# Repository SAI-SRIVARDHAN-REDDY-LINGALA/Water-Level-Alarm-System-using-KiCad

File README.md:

# Water Level Alarm System using KiCad

## Overview

This project implements a simple and practical **Water Level Alarm System** designed using **KiCad PCB Design Suite**.

The system detects the presence of water using conductive sensing probes and activates an alarm or buzzer when water reaches a predefined level.

The project focuses on:

- Basic electronic sensing principles
- PCB schematic design
- PCB layout design
- Practical embedded hardware thinking
- Signal detection circuits
- Real-world safety and monitoring applications

The complete design was developed using:

- KiCad Schematic Editor
- KiCad PCB Layout Designer

---

# Features

- Water level detection
- Conductive probe sensing
- Alarm/buzzer indication
- Compact PCB design
- Practical low-cost implementation
- Real-world utility application
- PCB layout using KiCad
- Schematic capture
- Hardware-oriented design flow
- Beginner-friendly embedded electronics project

---

# Technologies Used

- KiCad EDA
- PCB Design
- Schematic Capture
- Electronic Circuit Design
- Sensor Interface Concepts
- Embedded Hardware Design

---

# Problem Statement

Water overflow in:

- tanks
- storage systems
- industrial containers
- home water systems

can cause:

- water wastage
- equipment damage
- electrical hazards

This project provides a simple electronic monitoring solution to alert users when water reaches a specific level.

---

# Working Principle

Water conducts electricity due to dissolved ions.

The system uses conductive probes placed at different water levels.

When water touches the sensing probes:

```text
Electrical path completes
        ↓
Detection circuit activates
        ↓
Alarm/Buzzer turns ON
```

---

# System Architecture

```text
Water Probes
      ↓
Detection Circuit
      ↓
Signal Activation
      ↓
Buzzer / Alarm
```

---

# Hardware Design Flow

The project follows a standard PCB development workflow:

```text
Circuit Design
      ↓
Schematic Capture
      ↓
Component Placement
      ↓
PCB Routing
      ↓
Design Rule Check (DRC)
      ↓
Final PCB Layout
```

---

# Schematic Design

The schematic includes:

- Water sensing probes
- Detection circuitry
- Output alarm device
- Power connections
- Signal routing

The design captures all electrical connectivity before PCB implementation.

---

# PCB Design

The PCB layout was developed in KiCad with focus on:

- Proper component placement
- Clean routing
- Electrical connectivity
- Compact board organization
- Manufacturable PCB structure

---

# PCB Design Concepts Covered

- PCB routing
- Component footprints
- Net connectivity
- Copper traces
- Signal paths
- Board layout planning
- Electrical rule validation
- Design Rule Check (DRC)

---

# Embedded Electronics Concepts Demonstrated

- Sensor-based detection
- Analog signal triggering
- Conductive sensing
- Alarm systems
- Hardware interfacing
- Practical electronic circuit behavior

---

# Skills Demonstrated

- KiCad PCB Design
- Schematic Capture
- PCB Layout Design
- Electronic Circuit Design
- Hardware System Thinking
- Sensor Interface Design
- Embedded Hardware Fundamentals
- Practical Electronics Prototyping

---

# Real-World Applications

This type of system is used in:

- Water tanks
- Industrial liquid monitoring
- Home automation systems
- Safety monitoring devices
- Overflow prevention systems
- Smart water management systems

---

# Engineering Importance

Although simple, this project introduces important hardware engineering workflows including:

- Schematic-to-PCB flow
- Real sensor interfacing
- Electrical connectivity planning
- Practical embedded system design
- Hardware debugging concepts

These are foundational skills for:

- Embedded systems engineering
- PCB design engineering
- Electronics product development
- IoT hardware systems

---

# Industry Relevance

The concepts demonstrated here are foundational to:

- Embedded electronics
- IoT sensing systems
- Industrial monitoring systems
- Consumer electronics hardware
- PCB-based product design

---

# Key Takeaways

- Water can be used as a conductive sensing medium
- PCB design begins with proper schematic capture
- KiCad provides a complete open-source PCB workflow
- Simple sensor systems require both electrical and physical design thinking
- Hardware design involves both circuit functionality and manufacturable layout planning

---

# Final Core Insight

```text
Sensor Detection
+
Signal Processing
+
PCB Implementation
=
Practical Embedded Hardware System
```

---

# Author

**Sai Srivardhan Lingala**  
Electronics Engineering Student | FPGA & Embedded Hardware Enthusiast

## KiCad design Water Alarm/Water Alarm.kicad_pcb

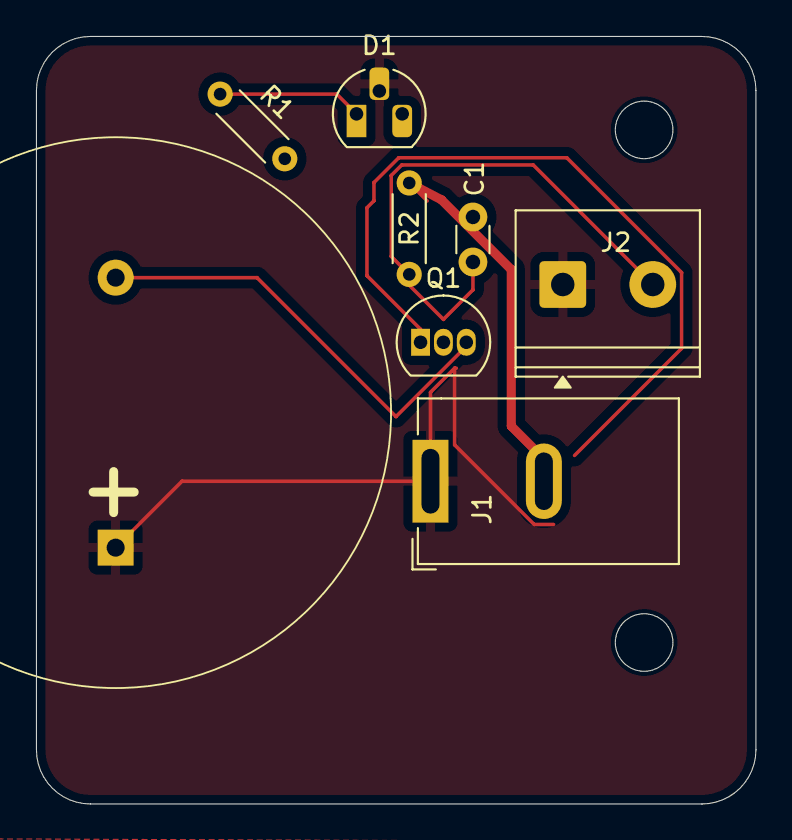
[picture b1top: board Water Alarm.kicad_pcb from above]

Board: 2 copper layers, 40.0 x 42.6 mm, 8 parts (0 on the bottom side), 5 nets.

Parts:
BZ1: Buzzer; Buzzer_D30mm_H20mm_P15mm__668-1652-ND__AI-3035-TT-12V-R
C1: 1nF; C_Disc_D3.0mm_W1.6mm_P2.50mm
D1: LED_Small_Filled; TO-92L_HandSolder
J1: Jack-DC; BarrelJack_GCT_DCJ200-10-A_Horizontal
J2: Screw_Terminal_01x02; TerminalBlock_Phoenix_PT-1,5-2-5.0-H_1x02_P5.00mm_Horizontal
Q1: 2N7000; TO-92_Inline
R1: 6.8k; R_Axial_DIN0204_L3.6mm_D1.6mm_P5.08mm_Horizontal
R2: 10M; R_Axial_DIN0204_L3.6mm_D1.6mm_P5.08mm_Horizontal

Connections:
/Gate: C1.1, J2.2, Q1.2 (G), R2.1
GND: C1.2, J1.2, Q1.1 (S), R1.2, R2.2
unnamed: BZ1.2 (-), Q1.3 (D)
unnamed: D1.1 (K), R1.1
VCC: BZ1.1 (+), D1.2 (A), J1.1, J2.1

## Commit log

2026-05-14 Revise README for Water Level Alarm System project
    Updated project title and added detailed sections on overview, features, technologies, problem statement, working principle, system architecture, hardware design flow, schematic design, PCB design, a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
